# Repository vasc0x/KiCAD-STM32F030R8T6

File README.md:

# KiCAD-STM32F030R8T6
Breakout board for the ARM Cortex M0 STM32F030R8T6 (LQFP64)

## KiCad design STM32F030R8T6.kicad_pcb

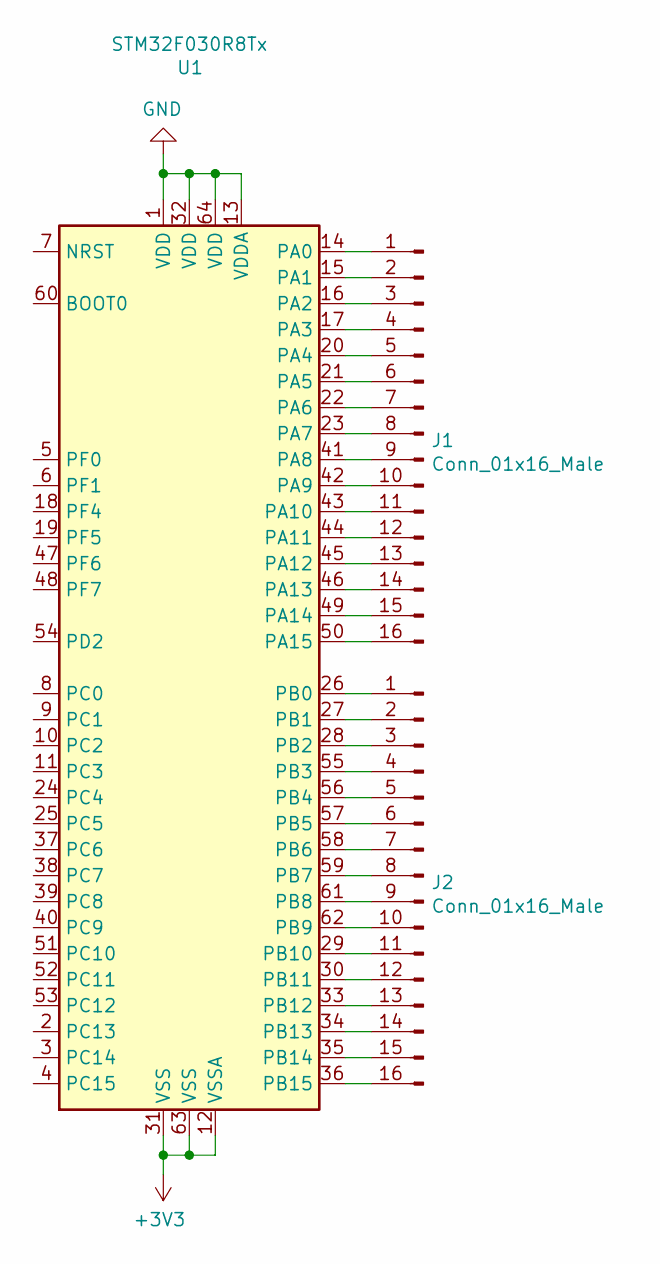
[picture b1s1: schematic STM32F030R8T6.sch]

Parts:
J1, J2: Conn_01x16_Male; PinHeader_1x16_P2.54mm_Vertical
U1: STM32F030R8Tx; LQFP-64_10x10mm_P0.5mm

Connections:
+3V3: U1.12 (VSSA), U1.31 (VSS), U1.63 (VSS)
GND: U1.1 (VDD), U1.13 (VDDA), U1.32 (VDD), U1.64 (VDD)
unnamed: J1.1, U1.14 (PA0)
unnamed: J1.2, U1.15 (PA1)
unnamed: J1.3, U1.16 (PA2)
unnamed: J1.4, U1.17 (PA3)
unnamed: J1.5, U1.20 (PA4)
unnamed: J1.6, U1.21 (PA5)
unnamed: J1.7, U1.22 (PA6)
unnamed: J1.8, U1.23 (PA7)
unnamed: J1.9, U1.41 (PA8)
unnamed: J1.10, U1.42 (PA9)
unnamed: J1.11, U1.43 (PA10)
unnamed: J1.12, U1.44 (PA11)
unnamed: J1.13, U1.45 (PA12)
unnamed: J1.14, U1.46 (PA13)
unnamed: J1.15, U1.49 (PA14)
unnamed: J1.16, U1.50 (PA15)
unnamed: J2.1, U1.26 (PB0)
unnamed: J2.2, U1.27 (PB1)
unnamed: J2.3, U1.28 (PB2)
unnamed: J2.4, U1.55 (PB3)
unnamed: J2.5, U1.56 (PB4)
unnamed: J2.6, U1.57 (PB5)
unnamed: J2.7, U1.58 (PB6)
unnamed: J2.8, U1.59 (PB7)
unnamed: J2.9, U1.61 (PB8)
unnamed: J2.10, U1.62 (PB9)
unnamed: J2.11, U1.29 (PB10)
unnamed: J2.12, U1.30 (PB11)
unnamed: J2.13, U1.33 (PB12)
unnamed: J2.14, U1.34 (PB13)
unnamed: J2.15, U1.35 (PB14)
unnamed: J2.16, U1.36 (PB15)

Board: 2 copper layers, 3 parts (0 on the bottom side), 34 nets, no tracks yet.

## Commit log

2020-01-22 added some headers
